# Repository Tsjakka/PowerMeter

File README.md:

# PowerMeter

ESP32-C3 project for measuring the power consumed per circuit breaker in your home.

PowerMeter measures the **real power and energy of each circuit (group) in a household fuse box**. A small current transformer clamps around the live wire of every circuit. Three dedicated energy-metering ICs sample all currents and the mains voltage **simultaneously**. An ESP32-C3 serves the results on a web page over Wi-Fi.

## Features

- **7 circuits + 2 spare channels** in a single-phase home, or **up to 3 circuits per phase (9 in total) in a three-phase home**. Each metering chip has its own voltage input; two solder jumpers (closed by default) link them for single-phase use.
- **True real power with sign**, so a circuit with a solar inverter shows production as negative power. Import and export energy are counted separately.
- **Energy-metering ICs do the maths.** Three Microchip **ATM90E32AS** sample every channel at 8 kHz and compute active/reactive power, RMS voltage/current, power factor and energy in hardware.
- **Web page on the ESP32-C3** (no Home Assistant required), plus an optional **128×64 OLED** and a **push button** for a local readout and Wi-Fi setup.
- **SELV only on the board.** No mains voltage reaches the PCB: the voltage reference comes from a 7 V AC plug-in adapter, power from a 5 V USB charger.
- **Designed for JLCPCB assembly.** All SMD parts are placed by JLCPCB; only the screw terminals and headers are hand-soldered.

## How it works

```
 CT (2000:1) ─► burden 2×22 Ω ─► RC 1k/33nF ─┐
 CT ... (9×)                                  ├─► 3× ATM90E32AS ──SPI──► ESP32-C3 SuperMini ──Wi-Fi──► web page
 7 V AC adapter ─► divider 22k/1k ─► RC ─────┘          ▲                        │
                                                 clean 3.3 V (LDO)        OLED (I²C) + button
 5 V USB ─► SS14 ─► SuperMini 5V pin + AP2112K-3.3 ─┘
```

| Item | Value |
|---|---|
| Current sensors | DL-CT08CL5, 2000:1 (20 A / 10 mA), solid-core |
| Measuring range per channel | ~5.5 mA … 32 A RMS (≈1.3 W … 7.5 kW at 230 V) |
| Burden / anti-aliasing | 2 × 22 Ω centre-tapped to GND, 1 kΩ + 33 nF C0G per input |
| Voltage sensing | One 7 V AC input per metering chip (L1 = CT1–3, L2 = CT4–6, L3 = CT7–9), each with a 22 kΩ / 1 kΩ divider phase-matched to the current inputs. JP1/JP2 closed = one adapter for all three |
| Metering ICs | 3 × ATM90E32AS (3 current + 3 voltage ADCs each, 16.384 MHz crystal) |
| Controller | ESP32-C3 SuperMini, plugged into female headers |
| Power | 5 V via a screw terminal (cut-off USB cable) |
| PCB | 140 × 98 mm, 2 layers, fits a Kradex Z74 (176 × 126 × 57 mm) enclosure |

### ESP32-C3 pin assignment

| Function | GPIO |
|---|---|
| SPI SCLK / MISO / MOSI | 4 / 5 / 6 |
| Chip select ATM 1 / 2 / 3 | 7 / 10 / 3 |
| OLED I²C SDA / SCL | 20 / 21 |
| Push button | 1 |
| Spare (test pad) | 0 |

## Repository contents

| Path | Contents |
|---|---|
| `Hardware/PowerMeter.kicad_pro` | KiCad 10 project: schematic (ERC clean) and routed PCB (DRC: 0 errors, 0 unconnected) |
| `Hardware/PowerMeter.kicad_sym`, `Hardware/PowerMeter.pretty/` | Project libraries: ATM90E32AS symbol, ESP32-C3 SuperMini symbol and socket footprint |
| `Hardware/PowerMeter_v2_schema.pdf` | Schematic as PDF |
| `Hardware/PowerMeter_v2_BOM.csv` | Full bill of materials with LCSC part numbers |
| `Hardware/Productie/` | JLCPCB order package: Gerber zip, assembly BOM and CPL, and ordering notes |
| `Hardware/Ontwerp_v2_ESP32-C3.md` | Full design document: calculations, layout rules, bring-up plan, ESPHome config (in Dutch) |
| `Hardware/CAMOutputs/` | Gerbers of the earlier v1 board (Raspberry Pi + ADS1115), kept for reference |

## Building one

1. **Order the PCB.** Upload `Hardware/Productie/PowerMeter_v2_Gerbers.zip`, `JLCPCB_BOM.csv` and `JLCPCB_CPL.csv` to JLCPCB (2 layers, 1.6 mm, top-side assembly).
   - Check part rotations in the placement preview, especially the three ATM90E32AS (pin 1 bottom-left) and the SOT-23-5 regulator.
   - See `Hardware/Productie/LEESMIJ_bestellen.md` for all settings.
2. **Hand-solder the through-hole parts:** 13 screw terminals (5.08 mm), the DC jack, 2 × 8-pin female headers for the SuperMini, and the OLED and button headers.
3. **Bring it up step by step:**
   - With only 5 V applied: check 3.3 V, and per chip VDD18 ≈ 1.8 V and Vref ≈ 1.2 V.
   - Then fit the SuperMini, connect the AC adapter and one CT.
   - Calibrate voltage and current against a multimeter and a known load (e.g. a kettle).
4. **Firmware.** Start with ESPHome. Its `atm90e32` component and `web_server` (version 3, with graphs) work without Home Assistant. A starting configuration is in the design document. Custom firmware with long-term history is planned.

## Safety

The PCB itself only carries safe low voltages, but **installing the CTs means working inside the fuse box**:

- **Switch off the main breaker.** The CTs are solid-core, so the wire of each circuit has to be disconnected to slide it through. Get a qualified electrician if you are unsure.
- **Measure only the live (L) wire** of each circuit.
- **Never connect or disconnect a CT while current flows through it.** The silkscreen warns about this, too.
- **Mount all CTs the same way round,** with the red wire in the left terminal. A reversed CT simply reads negative power.

## Status and background

- **Status:** design complete, PCB routed and ready to order (including the three-phase voltage inputs added on 10 November 2026); not yet built or tested.
- **v1:** an earlier attempt used a Raspberry Pi with ADS1115 ADCs and LM358 buffers. It never worked: two ADCs were on the same I²C address, the op-amps were not rail-to-rail, and the ADS1115 is too slow to sample voltage and current simultaneously.
- **Inspiration:** a friend's Arduino-based [energy logger](https://rands.nl/projects/logger.htm).

## License

[MIT](LICENSE)

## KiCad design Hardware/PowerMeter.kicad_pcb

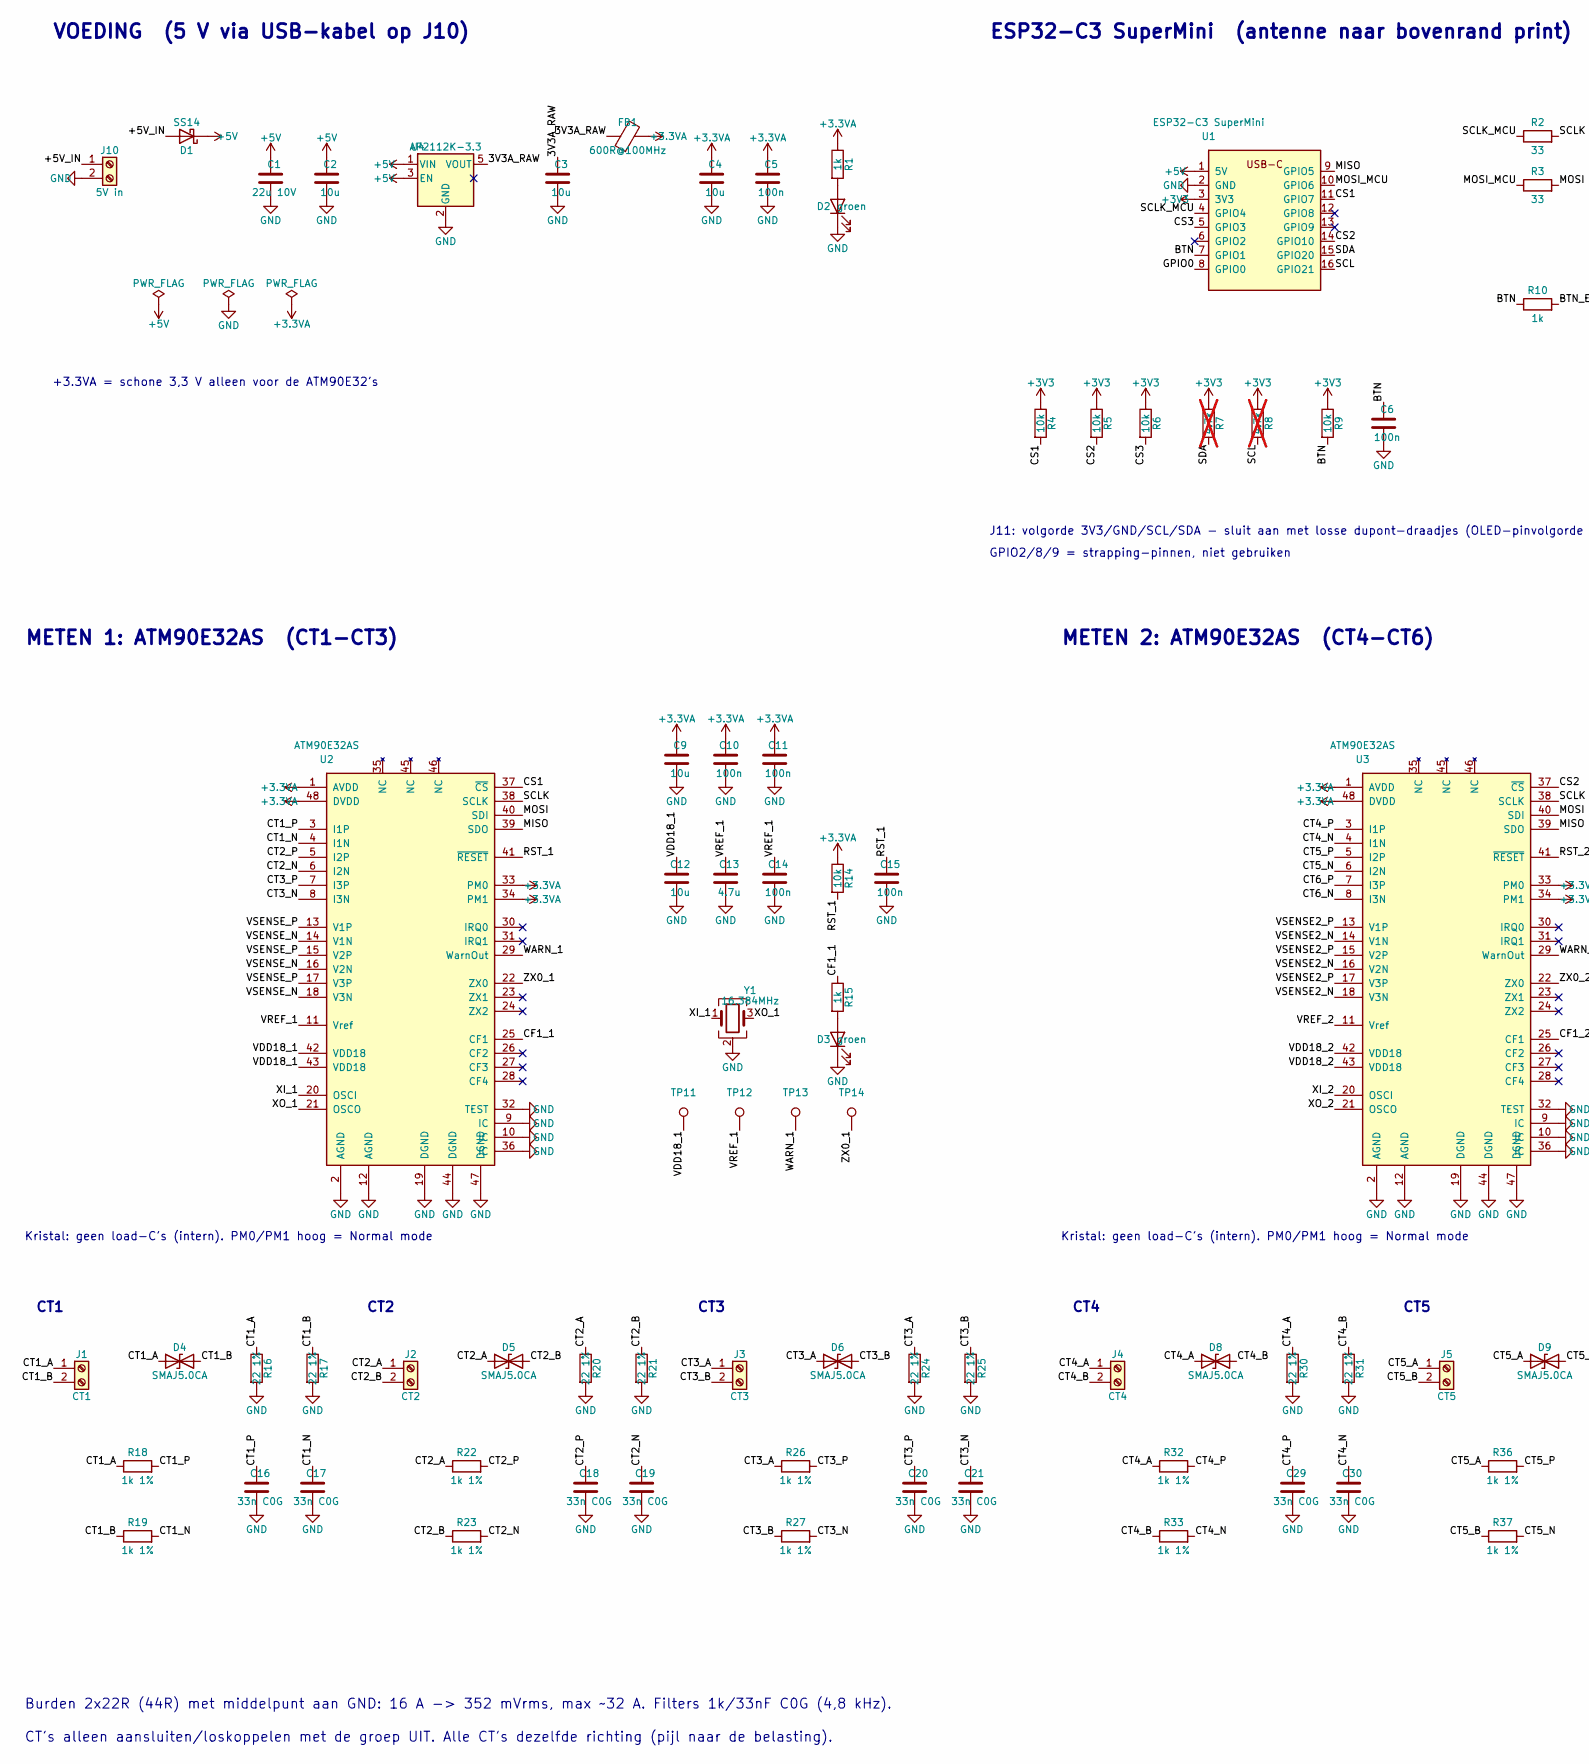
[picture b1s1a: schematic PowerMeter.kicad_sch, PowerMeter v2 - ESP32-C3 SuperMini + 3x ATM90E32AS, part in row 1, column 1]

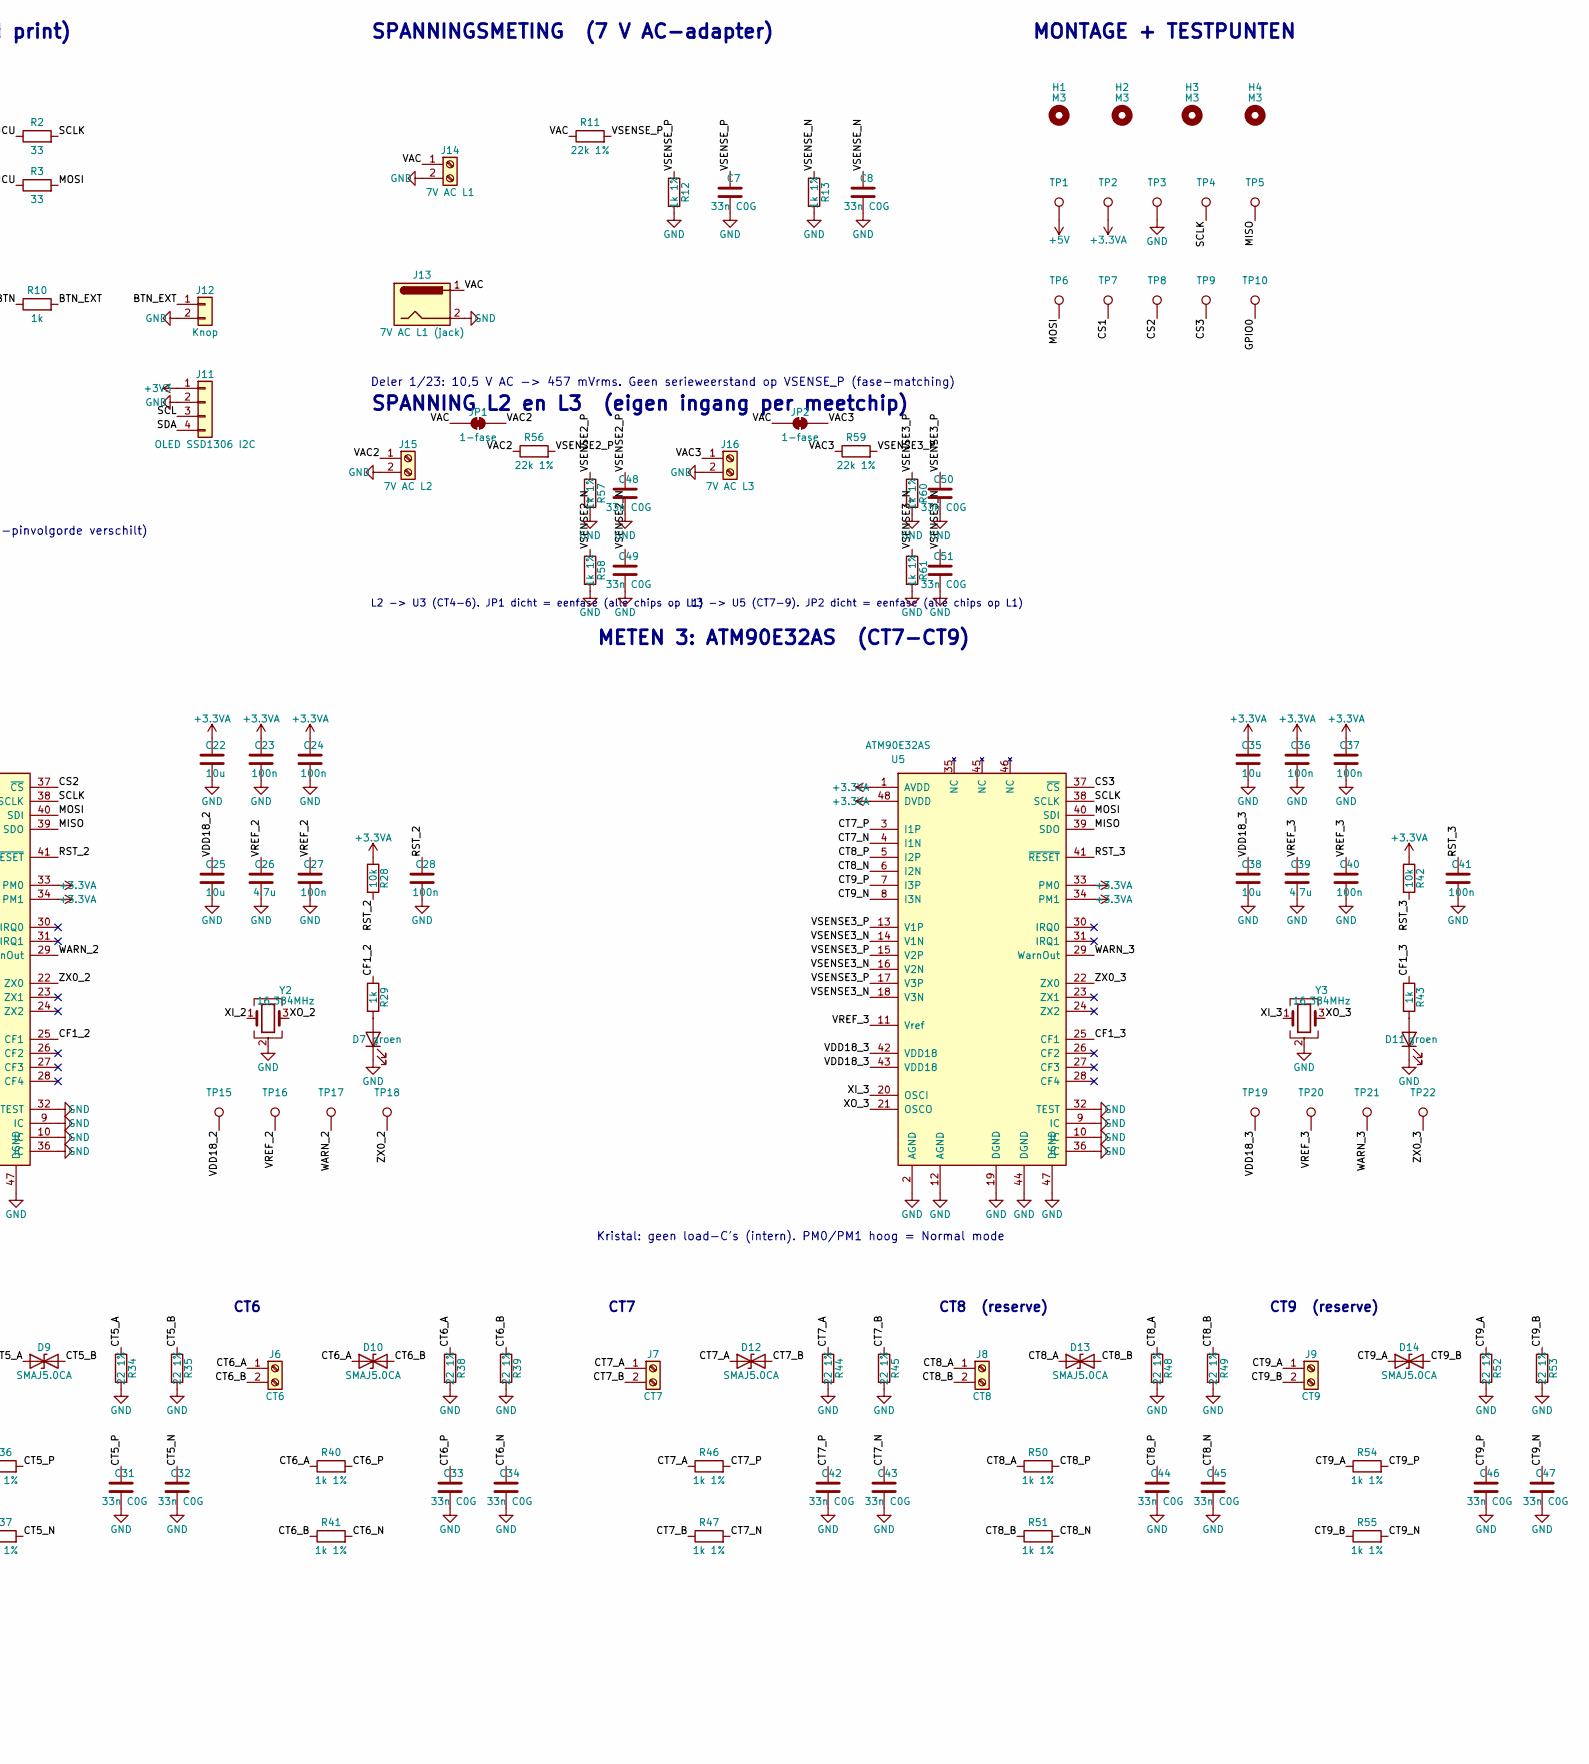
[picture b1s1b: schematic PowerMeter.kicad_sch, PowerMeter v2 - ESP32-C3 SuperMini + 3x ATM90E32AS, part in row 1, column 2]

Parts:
C1: 22u 10V; C_1206_3216Metric; LCSC C12891
C2, C3, C4, C9, C12, C22, C25, C35, C38: 10u; C_0805_2012Metric; LCSC C15850
C5, C6, C10, C11, C14, C15, C23, C24, C27, C28, C36, C37, C40, C41: 100n; C_0603_1608Metric; LCSC C14663
C7, C8, C16, C17, C18, C19, C20, C21, C29, C30, C31, C32, C33, C34, C42, C43, C44, C45, C46, C47, C48, C49, C50, C51: 33n C0G; C_0805_2012Metric; LCSC C1518212
C13, C26, C39: 4.7u; C_0805_2012Metric; LCSC C1779
D1: SS14; D_SMA; LCSC C2480
D2, D3, D7, D11: groen; LED_0805_2012Metric; LCSC C2297
D4, D5, D6, D8, D9, D10, D12, D13, D14: SMAJ5.0CA; D_SMA; LCSC C140894
FB1: 600R@100MHz; L_0805_2012Metric; LCSC C1017
H1, H2, H3, H4: M3; MountingHole_3.2mm_M3
J1: CT1; TerminalBlock_Phoenix_MKDS-1,5-2-5.08_1x02_P5.08mm_Horizont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
J2: CT2; TerminalBlock_Phoenix_MKDS-1,5-2-5.08_1x02_P5.08mm_Horizont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
J3: CT3; TerminalBlock_Phoenix_MKDS-1,5-2-5.08_1x02_P5.08mm_Horizont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
J4: CT4; TerminalBlock_Phoenix_MKDS-1,5-2-5.08_1x02_P5.08mm_Horizont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
J5: CT5; TerminalBlock_Phoenix_MKDS-1,5-2-5.08_1x02_P5.08mm_Horizont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
J6: CT6; TerminalBlock_Phoenix_MKDS-1,5-2-5.08_1x02_P5.08mm_Horizont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
J7: CT7; TerminalBlock_Phoenix_MKDS-1,5-2-5.08_1x02_P5.08mm_Horizont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
J8: CT8; TerminalBlock_Phoenix_MKDS-1,5-2-5.08_1x02_P5.08mm_Horizont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
J9: CT9; TerminalBlock_Phoenix_MKDS-1,5-2-5.08_1x02_P5.08mm_Horizont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
J10: 5V in; TerminalBlock_Phoenix_MKDS-1,5-2-5.08_1x02_P5.08mm_Horizont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
J11: OLED SSD1306 I2C; PinHeader_1x04_P2.54mm_Vertical
J12: Knop; PinHeader_1x02_P2.54mm_Vertical
J13: 7V AC L1 (jack); BarrelJack_Horizontal
J14: 7V AC L1; TerminalBlock_Phoenix_MKDS-1,5-2-5.08_1x02_P5.08mm_Horizont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
J15: 7V AC L2; TerminalBlock_Phoenix_MKDS-1,5-2-5.08_1x02_P5.08mm_Horizont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
J16: 7V AC L3; TerminalBlock_Phoenix_MKDS-1,5-2-5.08_1x02_P5.08mm_Horizont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
JP1, JP2: 1-fase; SolderJumper-2_P1.3mm_Bridged_RoundedPad1.0x1.5mm
R1, R10, R15, R29, R43: 1k; R_0603_1608Metric; LCSC C21190
R2, R3: 33; R_0603_1608Metric; LCSC C23140
R4, R5, R6, R9, R14, R28, R42: 10k; R_0603_1608Metric; LCSC C25804
R7, R8: 4.7k; R_0603_1608Metric; LCSC C23162; not fitted
R11, R56, R59: 22k 1%; R_0805_2012Metric; LCSC C17560
R12, R13, R18, R19, R22, R23, R26, R27, R32, R33, R36, R37, R40, R41, R46, R47, R50, R51, R54, R55, R57, R58, R60, R61: 1k 1%; R_0805_2012Metric; LCSC C17513
R16, R17, R20, R21, R24, R25, R30, R31, R34, R35, R38, R39, R44, R45, R48, R49, R52, R53: 22 1%; R_0805_2012Metric; LCSC C17561
TP1: +5V; TestPoint_Pad_D1.5mm
TP2: +3.3VA; TestPoint_Pad_D1.5mm
TP3: GND; TestPoint_Pad_D1.5mm
TP4: SCLK; TestPoint_Pad_D1.5mm
TP5: MISO; TestPoint_Pad_D1.5mm
TP6: MOSI; TestPoint_Pad_D1.5mm
TP7: CS1; TestPoint_Pad_D1.5mm
TP8: CS2; TestPoint_Pad_D1.5mm
TP9: CS3; TestPoint_Pad_D1.5mm
TP10: GPIO0; TestPoint_Pad_D1.5mm
TP11: VDD18_1; TestPoint_Pad_D1.5mm
TP12: VREF_1; TestPoint_Pad_D1.5mm
TP13: WARN_1; TestPoint_Pad_D1.5mm
TP14: ZX0_1; TestPoint_Pad_D1.5mm
TP15: VDD18_2; TestPoint_Pad_D1.5mm
TP16: VREF_2; TestPoint_Pad_D1.5mm
TP17: WARN_2; TestPoint_Pad_D1.5mm
TP18: ZX0_2; TestPoint_Pad_D1.5mm
TP19: VDD18_3; TestPoint_Pad_D1.5mm
TP20: VREF_3; TestPoint_Pad_D1.5mm
TP21: WARN_3; TestPoint_Pad_D1.5mm
TP22: ZX0_3; TestPoint_Pad_D1.5mm
U1: ESP32-C3 SuperMini; ESP32-C3_SuperMini_Socket
U2, U3, U5: ATM90E32AS; TQFP-48_7x7mm_P0.5mm; LCSC C177153
U4: AP2112K-3.3; SOT-23-5; LCSC C51118
Y1, Y2, Y3: 16.384MHz; Crystal_SMD_3225-4Pin_3.2x2.5mm; LCSC C13739

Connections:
+3.3VA: C4.1, C5.1, C9.1, C10.1, C11.1, C22.1, C23.1, C24.1, C35.1, C36.1, C37.1, FB1.2, R1.1, R14.1, R28.1, R42.1, TP2.1, U2.1 (AVDD), U2.33 (PM0), U2.34 (PM1), U2.48 (DVDD), U3.1 (AVDD), U3.33 (PM0), U3.34 (PM1), U3.48 (DVDD), U5.1 (AVDD), U5.33 (PM0), U5.34 (PM1), U5.48 (DVDD)
+3V3: J11.1, R4.1, R5.1, R6.1, R7.1, R8.1, R9.1, U1.3 (3V3)
+5V: C1.1, C2.1, D1.1 (K), TP1.1, U1.1 (5V), U4.1 (VIN), U4.3 (EN)
/3V3A_RAW: C3.1, FB1.1, U4.5 (VOUT)
/+5V_IN: D1.2 (A), J10.1
/BTN: C6.1, R9.2, R10.1, U1.7 (GPIO1)
/BTN_EXT: J12.1, R10.2
/CF1_1: R15.1, U2.25 (CF1)
/CF1_2: R29.1, U3.25 (CF1)
/CF1_3: R43.1, U5.25 (CF1)
/CS1: R4.2, TP7.1, U1.11 (GPIO7), U2.37 (~CS)
/CS2: R5.2, TP8.1, U1.14 (GPIO10), U3.37 (~CS)
/CS3: R6.2, TP9.1, U1.5 (GPIO3), U5.37 (~CS)
/CT1_A: D4.1 (A1), J1.1, R16.1, R18.1
/CT1_B: D4.2 (A2), J1.2, R17.1, R19.1
/CT1_N: C17.1, R19.2, U2.4 (I1N)
/CT1_P: C16.1, R18.2, U2.3 (I1P)
/CT2_A: D5.1 (A1), J2.1, R20.1, R22.1
/CT2_B: D5.2 (A2), J2.2, R21.1, R23.1
/CT2_N: C19.1, R23.2, U2.6 (I2N)
/CT2_P: C18.1, R22.2, U2.5 (I2P)
/CT3_A: D6.1 (A1), J3.1, R24.1, R26.1
/CT3_B: D6.2 (A2), J3.2, R25.1, R27.1
/CT3_N: C21.1, R27.2, U2.8 (I3N)
/CT3_P: C20.1, R26.2, U2.7 (I3P)
/CT4_A: D8.1 (A1), J4.1, R30.1, R32.1
/CT4_B: D8.2 (A2), J4.2, R31.1, R33.1
/CT4_N: C30.1, R33.2, U3.4 (I1N)
/CT4_P: C29.1, R32.2, U3.3 (I1P)
/CT5_A: D9.1 (A1), J5.1, R34.1, R36.1
/CT5_B: D9.2 (A2), J5.2, R35.1, R37.1
/CT5_N: C32.1, R37.2, U3.6 (I2N)
/CT5_P: C31.1, R36.2, U3.5 (I2P)
/CT6_A: D10.1 (A1), J6.1, R38.1, R40.1
/CT6_B: D10.2 (A2), J6.2, R39.1, R41.1
/CT6_N: C34.1, R41.2, U3.8 (I3N)
/CT6_P: C33.1, R40.2, U3.7 (I3P)
/CT7_A: D12.1 (A1), J7.1, R44.1, R46.1
/CT7_B: D12.2 (A2), J7.2, R45.1, R47.1
/CT7_N: C43.1, R47.2, U5.4 (I1N)
/CT7_P: C42.1, R46.2, U5.3 (I1P)
/CT8_A: D13.1 (A1), J8.1, R48.1, R50.1
/CT8_B: D13.2 (A2), J8.2, R49.1, R51.1
/CT8_N: C45.1, R51.2, U5.6 (I2N)
/CT8_P: C44.1, R50.2, U5.5 (I2P)
/CT9_A: D14.1 (A1), J9.1, R52.1, R54.1
/CT9_B: D14.2 (A2), J9.2, R53.1, R55.1
/CT9_N: C47.1, R55.2, U5.8 (I3N)
/CT9_P: C46.1, R54.2, U5.7 (I3P)
/GPIO0: TP10.1, U1.8 (GPIO0)
/MISO: TP5.1, U1.9 (GPIO5), U2.39 (SDO), U3.39 (SDO), U5.39 (SDO)
/MOSI: R3.2, TP6.1, U2.40 (SDI), U3.40 (SDI), U5.40 (SDI)
/MOSI_MCU: R3.1, U1.10 (GPIO6)
/RST_1: C15.1, R14.2, U2.41 (~RESET)
/RST_2: C28.1, R28.2, U3.41 (~RESET)
/RST_3: C41.1, R42.2, U5.41 (~RESET)
/SCL: J11.3, R8.2, U1.16 (GPIO21)
/SCLK: R2.2, TP4.1, U2.38 (SCLK), U3.38 (SCLK), U5.38 (SCLK)
/SCLK_MCU: R2.1, U1.4 (GPIO4)
/SDA: J11.4, R7.2, U1.15 (GPIO20)
/VAC: J13.1, J14.1, JP1.1 (A), JP2.1 (A), R11.1
/VAC2: J15.1, JP1.2 (B), R56.1
/VAC3: J16.1, JP2.2 (B), R59.1
/VDD18_1: C12.1, TP11.1, U2.42 (VDD18), U2.43 (VDD18)
/VDD18_2: C25.1, TP15.1, U3.42 (VDD18), U3.43 (VDD18)
/VDD18_3: C38.1, TP19.1, U5.42 (VDD18), U5.43 (VDD18)
/VREF_1: C13.1, C14.1, TP12.1, U2.11 (Vref)
/VREF_2: C26.1, C27.1, TP16.1, U3.11 (Vref)
/VREF_3: C39.1, C40.1, TP20.1, U5.11 (Vref)
/VSENSE2_N: C49.1, R58.1, U3.14 (V1N), U3.16 (V2N), U3.18 (V3N)
/VSENSE2_P: C48.1, R56.2, R57.1, U3.13 (V1P), U3.15 (V2P), U3.17 (V3P)
/VSENSE3_N: C51.1, R61.1, U5.14 (V1N), U5.16 (V2N), U5.18 (V3N)
/VSENSE3_P: C50.1, R59.2, R60.1, U5.13 (V1P), U5.15 (V2P), U5.17 (V3P)
/VSENSE_N: C8.1, R13.1, U2.14 (V1N), U2.16 (V2N), U2.18 (V3N)
/VSENSE_P: C7.1, R11.2, R12.1, U2.13 (V1P), U2.15 (V2P), U2.17 (V3P)
/WARN_1: TP13.1, U2.29 (WarnOut)
/WARN_2: TP17.1, U3.29 (WarnOut)
/WARN_3: TP21.1, U5.29 (WarnOut)
/XI_1: U2.20 (OSCI), Y1.1
/XI_2: U3.20 (OSCI), Y2.1
/XI_3: U5.20 (OSCI), Y3.1
/XO_1: U2.21 (OSCO), Y1.3
/XO_2: U3.21 (OSCO), Y2.3
/XO_3: U5.21 (OSCO), Y3.3
/ZX0_1: TP14.1, U2.22 (ZX0)
/ZX0_2: TP18.1, U3.22 (ZX0)
/ZX0_3: TP22.1, U5.22 (ZX0)
GND: C1.2, C2.2, C3.2, C4.2, C5.2, C6.2, C7.2, C8.2, C9.2, C10.2, C11.2, C12.2, C13.2, C14.2, C15.2, C16.2, C17.2, C18.2, C19.2, C20.2, C21.2, C22.2, C23.2, C24.2, C25.2, C26.2, C27.2, C28.2, C29.2, C30.2, C31.2, C32.2, C33.2, C34.2, C35.2, C36.2, C37.2, C38.2, C39.2, C40.2, C41.2, C42.2, C43.2, C44.2, C45.2, C46.2, C47.2, C48.2, C49.2, C50.2, C51.2, D2.1 (K), D3.1 (K), D7.1 (K), D11.1 (K), J10.2, J11.2, J12.2, J13.2, J14.2, J15.2, J16.2, R12.2, R13.2, R16.2, R17.2, R20.2, R21.2, R24.2, R25.2, R30.2, R31.2, R34.2, R35.2, R38.2, R39.2, R44.2, R45.2, R48.2, R49.2, R52.2, R53.2, R57.2, R58.2, R60.2, R61.2, TP3.1, U1.2 (GND), U2.2 (AGND), U2.9 (IC), U2.10 (IC), U2.12 (AGND), U2.19 (DGND), U2.32 (TEST), U2.36 (IC), U2.44 (DGND), U2.47 (DGND), U3.2 (AGND), U3.9 (IC), U3.10 (IC), U3.12 (AGND), U3.19 (DGND), U3.32 (TEST), U3.36 (IC), U3.44 (DGND), U3.47 (DGND), U4.2 (GND), U5.2 (AGND), U5.9 (IC), U5.10 (IC), U5.12 (AGND), U5.19 (DGND), U5.32 (TEST), U5.36 (IC), U5.44 (DGND), U5.47 (DGND), Y1.2 (G), Y1.4 (G), Y2.2 (G), Y2.4 (G), Y3.2 (G), Y3.4 (G)
unnamed: D2.2 (A), R1.2
unnamed: D3.2 (A), R15.2
unnamed: D7.2 (A), R29.2
unnamed: D11.2 (A), R43.2

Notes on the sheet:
VOEDING (5 V via USB-kabel op J10)
+3.3VA = schone 3,3 V alleen voor de ATM90E32's
ESP32-C3 SuperMini (antenne naar bovenrand print)
J11: volgorde 3V3/GND/SCL/SDA - sluit aan met losse dupont-draadjes (OLED-pinvolgorde verschilt)
GPIO2/8/9 = strapping-pinnen, niet gebruiken
SPANNINGSMETING (7 V AC-adapter)
Deler 1/23: 10,5 V AC -> 457 mVrms. Geen serieweerstand op VSENSE_P (fase-matching)
MONTAGE + TESTPUNTEN
METEN 1: ATM90E32AS (CT1-CT3)
Kristal: geen load-C's (intern). PM0/PM1 hoog = Normal mode
CT1
CT2
CT3
METEN 2: ATM90E32AS (CT4-CT6)
CT4
CT5
CT6
METEN 3: ATM90E32AS (CT7-CT9)
CT7
CT8 (reserve)
CT9 (reserve)
Burden 2x22R (44R) met middelpunt aan GND: 16 A -> 352 mVrms, max ~32 A. Filters 1k/33nF C0G (4,8 kHz).
CT's alleen aansluiten/loskoppelen met de groep UIT. Alle CT's dezelfde richting (pijl naar de belasting).
SPANNING L2 en L3 (eigen ingang per meetchip)
L2 -> U3 (CT4-6). JP1 dicht = eenfase (alle chips op L1)
L3 -> U5 (CT7-9). JP2 dicht = eenfase (alle chips op L1)

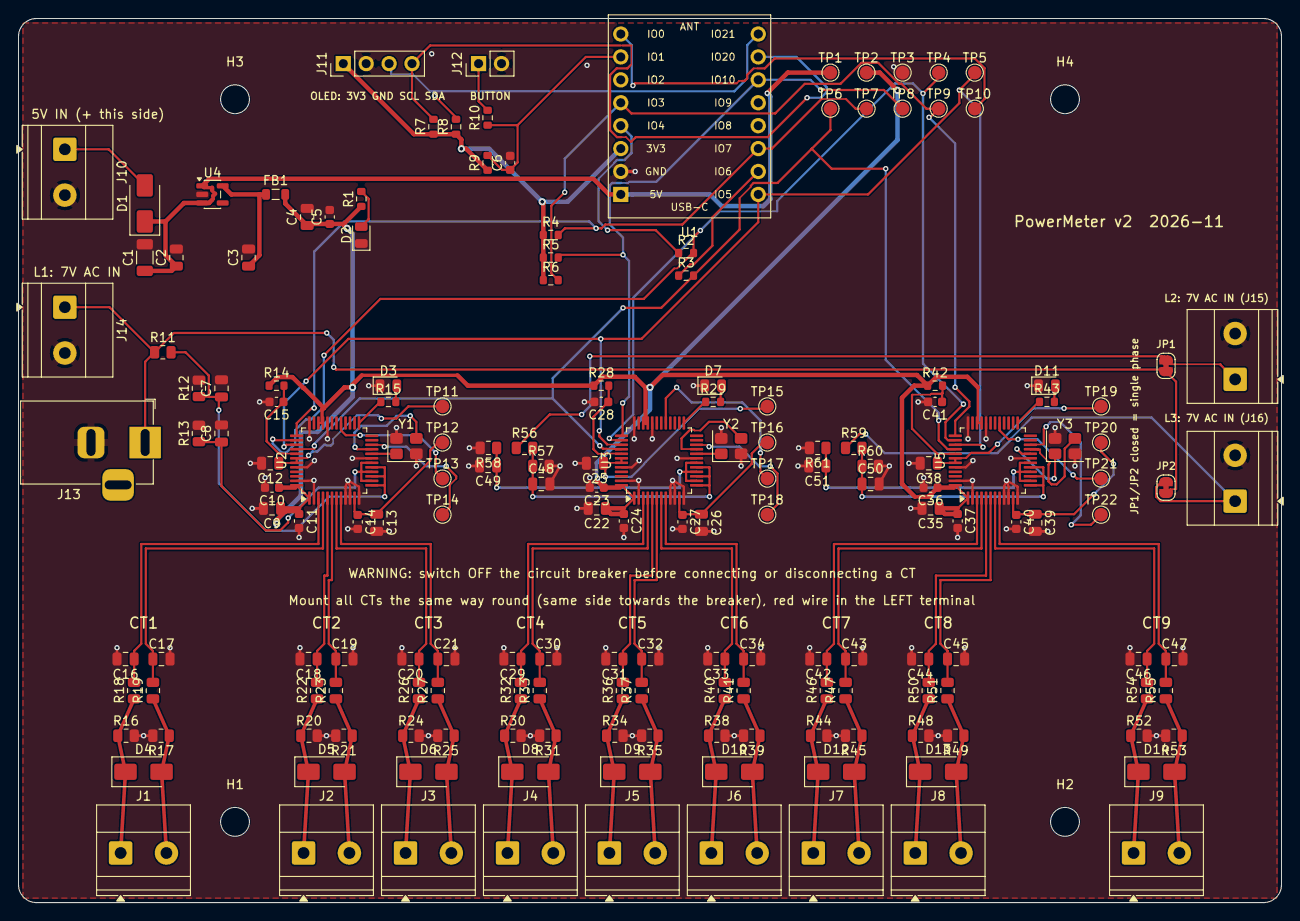
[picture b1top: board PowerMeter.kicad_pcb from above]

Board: 2 copper layers, 140.0 x 98.0 mm, 179 parts (0 on the bottom side), 92 nets.

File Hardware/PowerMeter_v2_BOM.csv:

"Designator","Value","Footprint","LCSC","Qty","DNP"
"C1","22u 10V","Capacitor_SMD:C_1206_3216Metric","C12891","1",""
"C2-C4,C9,C12,C22,C25,C35,C38","10u","Capacitor_SMD:C_0805_2012Metric","C15850","9",""
"C5,C6,C10,C11,C14,C15,C23,C24,C27,C28,C36,C37,C40,C41","100n","Capacitor_SMD:C_0603_1608Metric","C14663","14",""
"C7,C8,C16-C21,C29-C34,C42-C51","33n C0G","Capacitor_SMD:C_0805_2012Metric","C1518212","24",""
"C13,C26,C39","4.7u","Capacitor_SMD:C_0805_2012Metric","C1779","3",""
"D1","SS14","Diode_SMD:D_SMA","C2480","1",""
"D2,D3,D7,D11","groen","LED_SMD:LED_0805_2012Metric","C2297","4",""
"D4-D6,D8-D10,D12-D14","SMAJ5.0CA","Diode_SMD:D_SMA","C140894","9",""
"FB1","600R@100MHz","Inductor_SMD:L_0805_2012Metric","C1017","1",""
"J1","CT1","TerminalBlock_Phoenix:TerminalBlock_Phoenix_MKDS-1,5-2-5.08_1x02_P5.08mm_Horizontal","","1",""
"J2","CT2","TerminalBlock_Phoenix:TerminalBlock_Phoenix_MKDS-1,5-2-5.08_1x02_P5.08mm_Horizontal","","1",""
"J3","CT3","TerminalBlock_Phoenix:TerminalBlock_Phoenix_MKDS-1,5-2-5.08_1x02_P5.08mm_Horizontal","","1",""
"J4","CT4","TerminalBlock_Phoenix:TerminalBlock_Phoenix_MKDS-1,5-2-5.08_1x02_P5.08mm_Horizontal","","1",""
"J5","CT5","TerminalBlock_Phoenix:TerminalBlock_Phoenix_MKDS-1,5-2-5.08_1x02_P5.08mm_Horizontal","","1",""
"J6","CT6","TerminalBlock_Phoenix:TerminalBlock_Phoenix_MKDS-1,5-2-5.08_1x02_P5.08mm_Horizontal","","1",""
"J7","CT7","TerminalBlock_Phoenix:TerminalBlock_Phoenix_MKDS-1,5-2-5.08_1x02_P5.08mm_Horizontal","","1",""
"J8","CT8","TerminalBlock_Phoenix:TerminalBlock_Phoenix_MKDS-1,5-2-5.08_1x02_P5.08mm_Horizontal","","1",""
"J9","CT9","TerminalBlock_Phoenix:TerminalBlock_Phoenix_MKDS-1,5-2-5.08_1x02_P5.08mm_Horizontal","","1",""
"J10","5V in","TerminalBlock_Phoenix:TerminalBlock_Phoenix_MKDS-1,5-2-5.08_1x02_P5.08mm_Horizontal","","1",""
"J11","OLED SSD1306 I2C","Connector_PinHeader_2.54mm:PinHeader_1x04_P2.54mm_Vertical","","1",""
"J12","Knop","Connector_PinHeader_2.54mm:PinHeader_1x02_P2.54mm_Vertical","","1",""
"J13","7V AC L1 (jack)","Connector_BarrelJack:BarrelJack_Horizontal","","1",""
"J14","7V AC L1","TerminalBlock_Phoenix:TerminalBlock_Phoenix_MKDS-1,5-2-5.08_1x02_P5.08mm_Horizontal","","1",""
"J15","7V AC L2","TerminalBlock_Phoenix:TerminalBlock_Phoenix_MKDS-1,5-2-5.08_1x02_P5.08mm_Horizontal","","1",""
"J16","7V AC L3","TerminalBlock_Phoenix:TerminalBlock_Phoenix_MKDS-1,5-2-5.08_1x02_P5.08mm_Horizontal","","1",""
"R1,R10,R15,R29,R43","1k","Resistor_SMD:R_0603_1608Metric","C21190","5",""
"R2,R3","33","Resistor_SMD:R_0603_1608Metric","C23140","2",""
"R4-R6,R9,R14,R28,R42","10k","Resistor_SMD:R_0603_1608Metric","C25804","7",""
"R7,R8","4.7k","Resistor_SMD:R_0603_1608Metric","C23162","2","DNP"
"R11,R56,R59","22k 1%","Resistor_SMD:R_0805_2012Metric","C17560","3",""
"R12,R13,R18,R19,R22,R23,R26,R27,R32,R33,R36,R37,R40,R41,R46,R47,R50,R51,R54,R55,R57,R58,R60,R61","1k 1%","Resistor_SMD:R_0805_2012Metric","C17513","24",""
"R16,R17,R20,R21,R24,R25,R30,R31,R34,R35,R38,R39,R44,R45,R48,R49,R52,R53","22 1%","Resistor_SMD:R_0805_2012Metric","C17561","18",""
"U1","ESP32-C3 SuperMini","PowerMeter:ESP32-C3_SuperMini_Socket","","1",""
"U2,U3,U5","ATM90E32AS","Package_QFP:TQFP-48_7x7mm_P0.5mm","C177153","3",""
"U4","AP2112K-3.3","Package_TO_SOT_SMD:SOT-23-5","C51118","1",""
"Y1-Y3","16.384MHz","Crystal:Crystal_SMD_3225-4Pin_3.2x2.5mm","C13739","3",""
